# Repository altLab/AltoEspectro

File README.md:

# AltoEspectro

Projecto de Uma Camara de CCD arrefecida para Espectroscopia, imagem de scanning, ou para fotografia panorâmica se utilizada com cabeça panorâmica.

Assenta no Sensor CCD da Sony ILX 544A com ultra sensibilidade.

Tendo como unidade de génese de sinais, leitura da saída do sensor, controlo do arrefecimento termoeléctrico, e controlo de temperatura o Microcontrolador da Atmel Atmega 328 que faz parte do Arduino Nano.

Notas do projecto podem ser encontradas no MicroSite de Documentação do AltLab 

[aqui](http://altlab.org/d/s/projectos/altspectra/)

Projecto Iniciado por:

- Fernando Carvalho
- JAC
- Luis Dinis
- Pedro Angelo

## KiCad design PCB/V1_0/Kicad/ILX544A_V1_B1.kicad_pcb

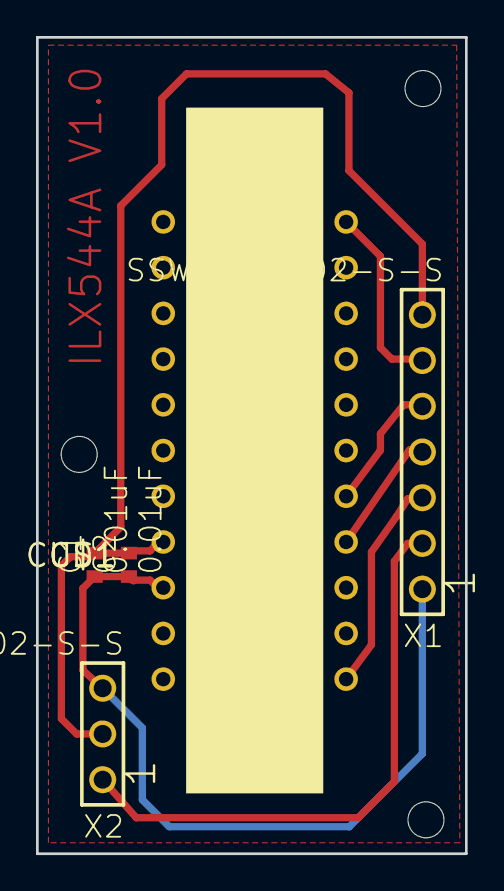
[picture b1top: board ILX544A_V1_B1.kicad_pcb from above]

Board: 2 copper layers, 23.8 x 45.4 mm, 8 parts (0 on the bottom side), 7 nets.

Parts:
@HOLE0, @HOLE1, @HOLE2: (no value)
C1, C2: 0.01uF; C0402
U$1: CCD1; ILX544A
X1: SSW-107-02-S-S
X2: SSW-103-02-S-S

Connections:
unnamed: C1.1, C2.1, U$1.P$20, X1.1, X2.3
unnamed: U$1.P$1, X1.3
unnamed: U$1.P$4, X1.4
unnamed: X1.2, X2.1
unnamed: U$1.P$11, X1.6
unnamed: U$1.P$5, X1.5
unnamed: C1.2, C2.2, U$1.P$19, X1.7, X2.2

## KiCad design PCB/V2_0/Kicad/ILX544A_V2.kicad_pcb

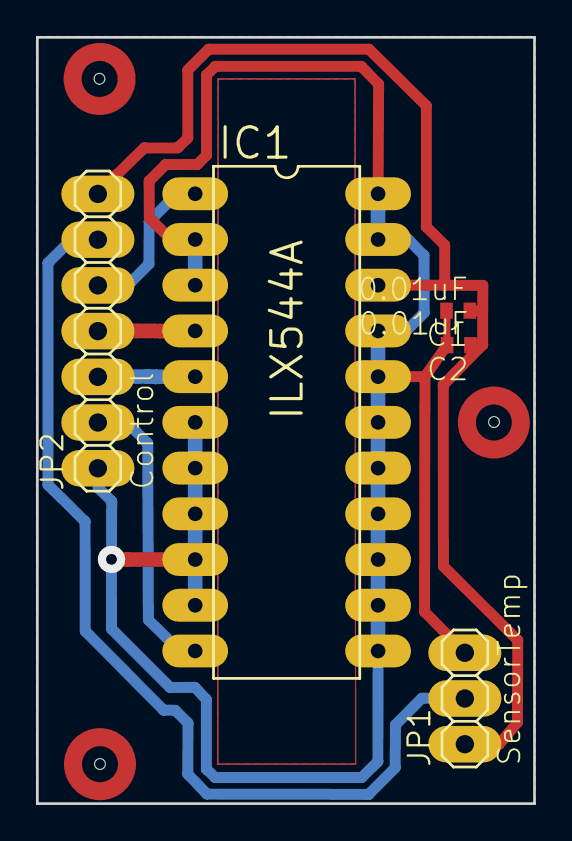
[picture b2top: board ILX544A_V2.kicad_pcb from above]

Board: 2 copper layers, 27.6 x 42.6 mm, 8 parts (0 on the bottom side), 7 nets.

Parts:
@HOLE0, @HOLE1, @HOLE2: (no value)
C1, C2: 0.01uF; C0402
IC1: ILX544A; DIL22-4
JP1: SensorTemp; 1X03
JP2: Control; 1X07

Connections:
unnamed: IC1.5, JP2.3
unnamed: C1.1, C2.1, IC1.20, JP1.1, JP2.7
unnamed: IC1.1, JP2.5
unnamed: IC1.4, JP2.4
unnamed: IC1.11, JP2.2
unnamed: JP1.2, JP2.6
unnamed: C1.2, C2.2, IC1.2, IC1.3, IC1.6, IC1.7, IC1.8, IC1.9, IC1.10, IC1.12, IC1.13, IC1.14, IC1.15, IC1.16, IC1.17, IC1.18, IC1.19, IC1.21, IC1.22, JP1.3, JP2.1

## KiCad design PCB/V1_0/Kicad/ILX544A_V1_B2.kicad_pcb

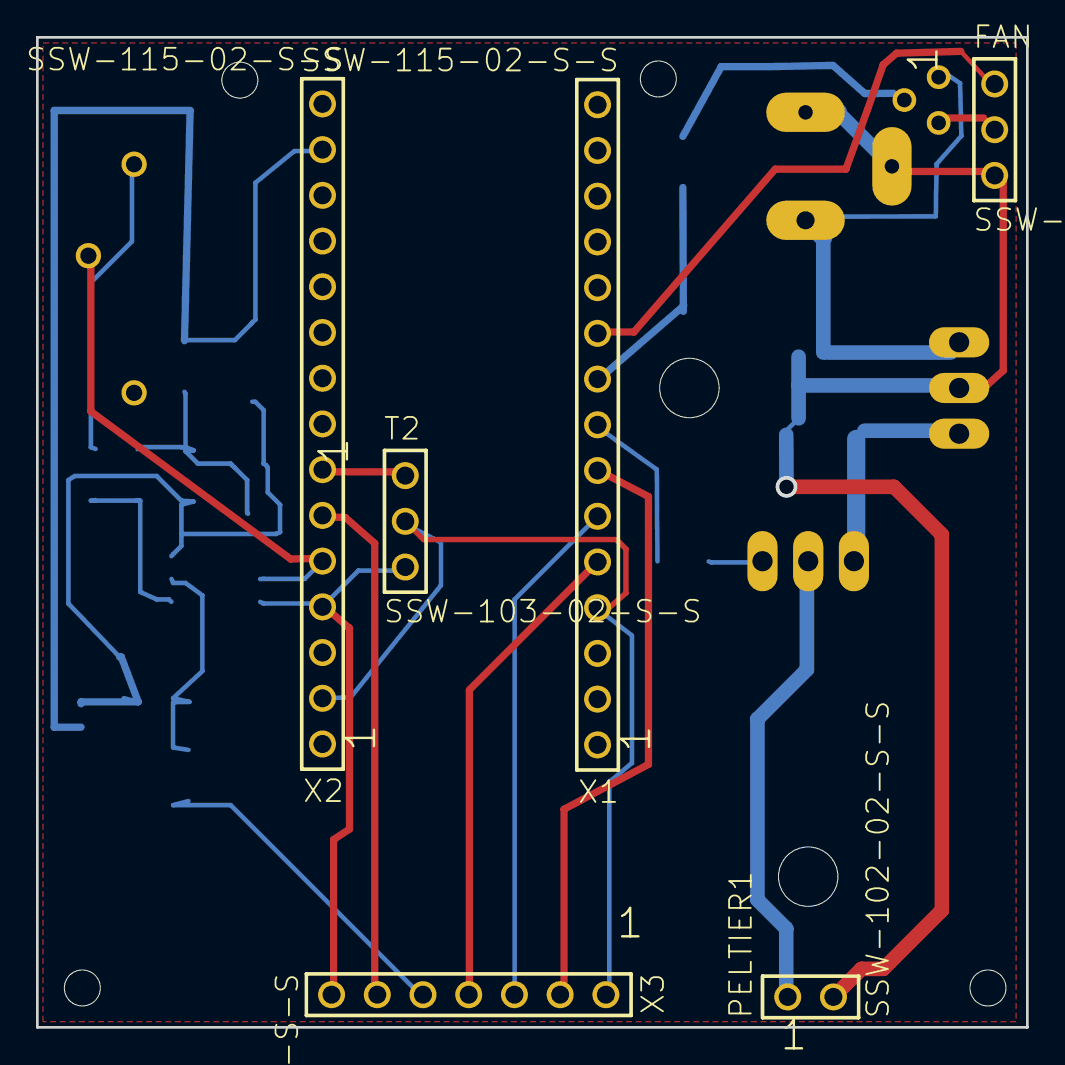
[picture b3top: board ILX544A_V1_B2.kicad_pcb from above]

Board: 2 copper layers, 55.0 x 55.0 mm, 29 parts (0 on the bottom side), 25 nets.

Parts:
@HOLE0, @HOLE1, @HOLE2, @HOLE3: (no value)
C1, C4: 22uF; 153CLV-0505
C2, C3: 10nF; C0402
FAN: SSW-103-02-S-S
IC1: 7805T; TO220H
P1: 2k; RTRIM43P
PELTIER1: SSW-102-02-S-S
Q1: BC517; TO92
Q3: TIP125; TO220
R1: 10; R1206
R2: 100K; R1206
R3: 2K9; R1206
R4: 1K; R1206
R5: 100; R1206
R6, R7, R8: 330; R1206
S1: S1; SPC4077
T2: SSW-103-02-S-S
U1: OPA350UA; SOIC127P600X175-8N
U$1: TL1; TL431CDBVRE4
X1, X2: SSW-115-02-S-S
X3: SSW-107-02-S-S

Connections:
GND: C1.-, C2.2, R2.1, R4.2, U1.4, U$1.REF
unnamed: P1.3, R5.1
unnamed: R3.1, R5.2, U1.2
unnamed: R1.1, R2.2, U1.3
unnamed: R3.2, R4.1, R6.2
unnamed: P1.2, U1.6, X2.5
unnamed: C3.1, IC1.1, Q1.3, S1.3
unnamed: C4.+, IC1.3, Q3.3
unnamed: R1.2, X3.5
unnamed: PELTIER1.1, Q3.2
unnamed: C3.2, C4.-, FAN.3, IC1.2, PELTIER1.2, S1.1, S1.2
unnamed: X2.6, X3.6
unnamed: Q3.1, R7.1
unnamed: X1.5, X3.4
unnamed: X1.6, X3.3
unnamed: X1.7, X3.2
unnamed: C1.+, C2.1, R6.1, X2.14
unnamed: FAN.2, Q1.1
unnamed: R7.2, X1.8
unnamed: FAN.1, X1.10
unnamed: Q1.2, R8.1
unnamed: R8.2, X1.9
unnamed: T2.2, X1.4, X2.2, X3.1
unnamed: T2.1, X2.7
VCC: T2.3, U1.7, X2.4, X3.7

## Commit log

2015-06-25 Versão de Base
    Controlo do relógio do ILX544A, inicio do protocolo de comandos entre o
    cliente e o AVR
2015-06-25 Add .gitignore
2015-06-25 Add a sketch of the serial protocol
2015-06-26 Upload of the main Sketches for Arduino and Processing
    upload of the Sketches that enable the temperature readouts, and
    ILX544Aoutput readout, and the graphing by processing
2015-06-27 Introducção dos documentos sobre o formato FITS
2015-06-27 SampleData
    introdução do ficheiro SampleData.txt com dados reais de um espectro,
    como se apresenta fotografia SampleData.PNG Para ser utilizado no
    desenvolvimento da aplicação ProcessingImager ou outra.
2015-06-28 Actualização da documentação
    alteração dos ficheiros de doccumentação para o formato markdown
2015-06-28 Introdução do documento sobre o arrefecimento
2015-06-28 Heatcalculation Document
    documento que explica as decisões tomadas na construção do sistema de
    dissipação de calor da camea
2015-07-01 Criação do Sketch para teste do control da fan
    Utiliza o Pin 6 para uma frequência de pwm de 980Hz de acordo com a
    datasheet do Atmega 328 e do código gerado pelo Arduino IDE para
    controlo de sinais PWM.
2015-07-01 Protocol Update
    Actualização do Protocolo de acordo com as necessidades encontradas na
    reunião de 30/06/2015
2015-07-01 minor corrections
2015-07-02 Actualização do Protocolo de texto
    actualização do ficheiro da descrição do protocolo, e do sketch para
    Arduino.
2015-07-02 tentativa de resolução da apresentação do documento com markdown
2015-07-03 Upload dos Esquemáticos e das Boards
2015-07-03 remoção justificada
    remoção devido à impossibilidade dos membros serem capazes de interagir
    com o sistema de modo coerente.
2015-07-03 Upload Eagle Files, gerbers and drills
2015-07-05 AltoEspectro - Firmware
    Implementação das funcionalidades de leitura de temperatura do peltier e
    do dissipador assim como da contagem de 1 millisegundo para actualização
    do timestamp.
2015-07-07 Markup correction test
2015-07-07 Stencils for Laser Printing V1_0
2015-07-07 Update com <BR> para resolver problema de apresentação no github
2015-07-07 Update do Protocolo
    inclusão do comando:
    - Get Status
    - Set Fan
2015-07-13 Cleaning of temp files
2015-07-13 Cleaning temp files 1
2015-07-13 Folder Structure Changed
    Implementation of folder structure for Versioning
2015-07-13 Correção ao esquemático
    Correção ao condensador da placa do sensor erro de tipografia
2015-07-13 Introdução da versão 2 das boards
2017-08-01 Make Eagle design files a subfolder of generic PCB design files
2017-08-01 Add Kicad versions of PCB board design files
